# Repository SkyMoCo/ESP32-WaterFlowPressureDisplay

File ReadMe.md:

# ESP32 Water Flow & Pressure Display

Firmware for an ESP32 that reads the well's flow meter and pressure sensor,
shows both on two 1.28" round displays, and publishes everything to MQTT.

It builds on [ESP32-Water-Meter-Monitor](../ESP32-Water-Meter-Monitor) and
keeps that project's pulse qualification, pressure math, NVS persistence and
MQTT topics and payloads, so existing dashboards and history carry on
unchanged. The display wiring follows
[The Solar Universe's two-GC9A01 build](https://thesolaruniverse.wordpress.com/2024/01/02/esp32-microcontroller-with-two-circular-240240-pixel-displays-gca901/),
with the pins moved off the ones the meter already uses.

## Hardware

- DOIT ESP32 DevKit V1 (ESP32-WROOM-32)
- EKM 3/4" pulse meter on GPIO 4, 0-100 PSI sensor on GPIO 34, status LED on
  GPIO 2. These are wired exactly as in the meter project, including the
  1k/100nF/100R flow front end and the 10k/10k pressure divider; see its
  ReadMe for why each part is there.
- 2 × 1.28" 240×240 round TFT, GC9A01 controller, 3.3 V, about 50 mA each

Every connection on one page, including the sensor front ends and the harness
notes for a permanent install: [hardware/WIRING.md](hardware/WIRING.md).

For a permanent install there is a carrier PCB that replaces the expansion
board and the harness. It has screw terminals for power, the sensors and the
LED, and headers for the displays. Gerbers, BOM and pick-and-place are ready
to order: [hardware/pcb](hardware/pcb/README.md).

### Display wiring

| ESP32 | Pressure display | Flow display |
|---|---|---|
| 3V3 | VCC | VCC |
| GND | GND | GND |
| GPIO 18 | SCL (SCLK) | SCL (SCLK) |
| GPIO 23 | SDA (MOSI) | SDA (MOSI) |
| GPIO 16 | DC | DC |
| GPIO 17 | RST | — |
| GPIO 27 | — | RST |
| GPIO 21 | CS | — |
| GPIO 22 | — | CS |
| (BL/BLK, if present) | 3V3 or unconnected | 3V3 or unconnected |

The article puts RST on GPIO 4 and DC on GPIO 2, but those pins are the flow
input and the LED here, so both move. GPIO 16/17 are free on a WROOM-32. On a
WROVER module they belong to the PSRAM, and DC/RST would need other pins
(update `platformio.ini`).

Both displays share every line except CS and RST. The firmware resets both,
then brings both CS pins low for `tft.init()` so both controllers get the init
sequence together. After that, each draw selects only one of them.

RST could be shared as well, since the displays are always reset together, but
one pin per display avoids a Y-split jumper. To share it, wire both RST pins to
GPIO 17 and set `DISPLAY_RST_FLOW` to 17 too.

## Displays

- **Left dial, pressure.** 0-100 PSI arc. It is green between
  `GAUGE_PSI_LOW` and `GAUGE_PSI_HIGH` (30 and 70 by default), red below that
  range and orange above it. Set the thresholds just outside your pressure
  switch's cut-in and cut-out. The footer shows `ONLINE`, `NO MQTT` or
  `NO WIFI`. If the sensor voltage leaves its valid range (open or shorted
  wire), the dial shows `--` and `SENSOR FAULT`.
- **Right dial, flow.** 0-20 GPM arc, with the running gallon total in the
  footer. The arc turns red above `MAX_PLAUSIBLE_GPM`.

The gauge reads flow from the time between the last two pulses. The 5 s
interval average moves in 0.9 GPM steps at low flow, which is too coarse and
slow for a needle. When pulses stop, the reading decays toward zero and reaches
zero after `FLOW_TIMEOUT_MS` (60 s).

Arcs are repainted in place and the numbers are drawn to off-screen sprites,
so the displays don't flicker.

## Demo mode

For bench testing with only the ESP32 and the displays wired up:

```
pio run -e demo -t upload
```

In the VS Code PlatformIO sidebar, use **demo → Upload**.

This builds the same firmware with simulated sensors. Every 2-6 s it picks a
new random pressure and flow and moves toward them smoothly. Some picks land
in the low and high pressure zones, above `MAX_PLAUSIBLE_GPM`, or in a sensor
fault, so every display state appears within a minute or two. The gallon total
starts at 12,345 and rises with the simulated flow. The dial titles read
`DEMO PRESSURE` and `DEMO FLOW` in amber.

Demo mode is kept separate from real data:

- **MQTT:** it publishes to `ranch/water-demo/*` as client
  `pumphouse-esp32-demo`. Fake numbers never reach the real topics, and it
  doesn't disconnect the real board.
- **Saved total:** it never reads or writes flash, so the real board's gallon
  total is safe if you reuse this ESP32 later.
- **Flow input:** GPIO 4 is left unused. With no pull-up resistor fitted, the
  pin would float and count noise as pulses.

Flash the default `esp32doit-devkit-v1` env for real use.

## MQTT

Topics and payloads are the same as in the meter project, with two added
fields:

- `ranch/water/flow`: adds `gpm_inst`, the pulse-period rate the gauge shows,
  next to the existing interval-average `gpm`
- `ranch/water/pressure`: adds `sensor_ok`. Its `psi`/`volts` values are now a
  ~0.5 s moving average instead of a single ADC read.
- `ranch/water/diag` and `ranch/water/status` are unchanged. The boot message
  ends with `display=dual_gc9a01`.

WiFi and MQTT run in their own FreeRTOS task on core 0, so reconnect attempts
never stall the displays.

## Setup

1. Copy [include/secrets.h.template](include/secrets.h.template) to
   `include/secrets.h` and fill it in. It is gitignored.
2. **Client ID:** if this board replaces the old one, leave `MQTT_CLIENT_ID`
   as `pumphouse-esp32`. If both will run at once, change it. Two clients with
   the same ID keep disconnecting each other.
3. **Running total:** the total is stored in the board's own flash, so a
   fresh board starts at 0 gallons. Read the old board's `pulse_count` from
   MQTT before swapping if you want to carry it over.
4. Build and upload with PlatformIO (env `esp32doit-devkit-v1`). TFT_eSPI is
   configured entirely through `build_flags` in
   [platformio.ini](platformio.ini), so don't edit the library's
   `User_Setup.h`.

If the image is mirrored or colours are wrong on your particular modules, try
`DISPLAY_ROTATION` in `main.cpp`, or add `-D TFT_RGB_ORDER=TFT_BGR` /
`-D TFT_INVERSION_ON` to `build_flags`.

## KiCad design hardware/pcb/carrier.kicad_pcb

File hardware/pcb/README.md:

# Carrier PCB

A 2-layer board that replaces the stock ESP32 expansion board and the dupont
harness. The DevKit plugs into it, field wiring lands on screw terminals, and
the displays plug into pin headers.

**To order:** upload [fab/carrier_gerbers.zip](fab/carrier_gerbers.zip) to
JLCPCB, PCBWay or similar. The defaults are fine: 2 layers, 1.6 mm, 1 oz,
HASL. Nothing on this board needs tighter than 0.2 mm track/space or a
0.3 mm via drill.

**For SMD assembly at JLCPCB:** tick *PCB Assembly*, top side, and upload
[fab/carrier_bom_jlc.csv](fab/carrier_bom_jlc.csv) and
[fab/carrier_cpl_jlc.csv](fab/carrier_cpl_jlc.csv). In the placement preview,
check that **Q1**, **D1** (cathode band toward Q1) and **F1** sit on their
pads the right way round. JLC's rotation conventions sometimes differ from
KiCad's for SOT-23 and SMA. Everything through-hole you solder yourself.

## Board

67 × 54 mm. The case's bay was sized around the 67 × 51 expansion board, so
set `exp_wid` to 54 in the case `CONFIG`. See [what the case needs](#the-case).

```
  ┌──────────────────────────────────────────────────────────┐
  │ ○  [J5 pressure disp] [J6 flow disp]   [J7 I2C]        ○ │  headers
  │     ════ channel: SPI bus to both headers ════            │
  │     [ DevKit top row: 1.0in ]                    ┌──────┐ │
  │     [ DevKit top row: 0.9in ]                    │ no   │ │
  │ USB    R6 R7 (I2C pull-ups)                      │copper│ │  DevKit sits
  │ <-     C5                                        │ (ant-│ │  over this,
  │        R5 R1 C3 R2         R3 R4 C4              │ enna)│ │  8.5 mm up
  │     [ DevKit bottom row ]                        └──────┘ │
  │       LED  G FLOW G +5V G SIG   G +5V    F1 Q1 R8 C1 C2   │
  │ ○    [J4 ] [J2   ] [J3       ] [J1  ]    D1             ○ │  terminals
  └──────────────────────────────────────────────────────────┘
          wires enter from the bottom edge
```

- **DevKit (U1):** two 1×15 female headers, USB toward the left wall. The
  bottom row is fixed. The top row has two footprints: one for 1.0" (25.4 mm,
  DOIT DevKit V1) and one for 0.9" (22.86 mm) clones. **Solder a socket into
  only one of them.** The silk marks which is which.
- **Antenna:** neither copper layer has anything under the WROOM antenna end,
  so the ground pour doesn't detune it.
- **Parts under the DevKit:** the 0603 resistors and capacitors sit under the
  DevKit. That's fine because the DevKit sits 8.5 mm up on its sockets.

## Connectors

### Screw terminals: 3.5 mm pitch, wires enter from the board edge

| Ref | Pins (left → right) | Goes to |
|---|---|---|
| J4 LED | LED, G | external status LED, anode to LED. **R5 330 Ω is on the board**, so don't add another. |
| J2 FLOW | FLOW, G | EKM reed switch, either way round. Armor/shield to G here only. |
| J3 PRESSURE | +5V, G, SIG | 0-100 PSI transducer: red, black, signal |
| J1 5V IN | G, +5V | regulated 5 V supply, about 250 mA. **Note G is on the left.** |

Footprint is Phoenix PT 1,5/x-3.5-H. The common blue/green "KF350" / "DB128"
3.5 mm terminals fit the same holes. Buy 2-pin and 3-pin, or click 2-pin
blocks together.

### Headers: 2.54 mm, male

| Ref | Pins (left → right) |
|---|---|
| J5 pressure display | GND, VCC, SCL, SDA, RES, DC, CS |
| J6 flow display | GND, VCC, SCL, SDA, RES, DC, CS |
| J7 I2C | GND, 3V3, SCL, SDA |

J5/J6 follow the pin order printed on the common 7-pin GC9A01 modules, so a
7-way dupont ribbon goes straight across. If your module has an 8th BLK pin,
leave it unconnected; the module pulls it up. **Check your module's order
against the silk before plugging in.** Some makers order them differently, and
then you cross the wires in the ribbon.

## Circuit

Every DevKit pin is the same one the firmware already uses
([src/main.cpp](../../src/main.cpp)), so **no firmware change is needed**.

| Net | DevKit pin | Parts |
|---|---|---|
| FLOW_GPIO | GPIO 4 | R1 1k to 3V3, C3 100 nF to GND, R2 100 Ω to J2 FLOW (the WIRING.md front end) |
| PRES_ADC | GPIO 34 | R3 10k from J3 SIG, R4 10k to GND, C4 100 nF to GND |
| LED_GPIO | GPIO 2 | R5 330 Ω to J4 LED |
| SCLK / MOSI / DC | GPIO 18 / 23 / 16 | both display headers |
| RST_P / CS_P | GPIO 17 / 21 | J5 |
| RST_F / CS_F | GPIO 27 / 22 | J6 |
| SDA / SCL | GPIO 25 / 26 | J7, with R6/R7 4k7 pull-ups to 3V3 |
| +5V | VIN | J3 sensor supply, from J1 through F1, Q1 |
| +3V3 | 3V3 | displays, J7, R1, pull-ups. C5 10 µF bulk. |

**C4 is new.** It's a 100 nF filter across the ADC input. With the 5 kΩ
divider it settles in about 0.5 ms, far faster than the firmware's 0.5 s
average, and it gives the ADC's sampling capacitor a low-impedance source.

### Power input

```
 J1 +5V ──F1 500mA PTC──┬── Q1 AO3401A (P-FET) ──┬── +5V → DevKit VIN, J3
                        │   D        S           │
                     D1 SMAJ5.0A           G ─R8 10k─ GND
                        │                        C1 10µ, C2 100n
                       GND
```

- **Reversed supply:** Q1 stays off and nothing downstream sees it.
  D1 conducts and trips F1.
- **Spike or overvoltage:** D1 clamps it. Unlike a series diode, the
  P-FET drops only millivolts, so the pressure sensor still gets the full
  5 V its 0.5-4.5 V output is scaled against.
- **USB and J1 at the same time:** this is normally fine. DOIT-style DevKits
  have a diode between USB 5 V and VIN, so J1 can't back-feed your computer.
  Clones vary, so check yours has one: a diode on the board next to the USB
  socket. Until you've checked, unplug J1 while programming over USB.

## Parts you solder

| Qty | Part |
|---|---|
| 2 | 1×15 female header, 2.54 mm, 8.5 mm tall (one bottom row, one top row) |
| 2 | 1×7 male header, 2.54 mm |
| 1 | 1×4 male header, 2.54 mm |
| 3 | 2-pin 3.5 mm screw terminal |
| 1 | 3-pin 3.5 mm screw terminal |

Fab-assembled SMD parts are in [the BOM](fab/carrier_bom_jlc.csv). All are
JLCPCB Basic parts except F1 (C315893) and D1 (C83329), which are Extended
and add a small loading fee. Any 1206 PTC around 500 mA hold, and any SMA
5.0 V-standoff unidirectional TVS, will do if those are out of stock.

## The case

Things that change in [../case](../case):

- `exp_wid` 51 → 54. The bay grows 3 mm.
- **The barrel-jack and board-USB holes are no longer needed.** The DevKit USB
  hole stays where it is: the DevKit still points its USB at the left wall,
  centred on the board.
- **Add a cable slot in the bottom wall**, under the terminal row. It spans
  x 11-46 mm from the board's left edge. Measure the wire-entry height on
  your terminal blocks; it's typically 3-6 mm above the board surface.

## Rebuilding

The board is generated, not drawn. Both scripts run in KiCad 10's Python:

```
"%LOCALAPPDATA%\Programs\KiCad\10.0\bin\python.exe" build_pcb.py
"%LOCALAPPDATA%\Programs\KiCad\10.0\bin\python.exe" make_outputs.py
```

[build_pcb.py](build_pcb.py) places and routes everything from the constants
at the top: pin map, terminal order, header positions. It also writes the
DevKit socket footprint into `carrier.pretty/`. [make_outputs.py](make_outputs.py)
refills the ground pours, **refuses to continue unless DRC is clean**, then
writes the Gerbers, drill files, zip, BOM, CPL and renders into `fab/`.

You can open `carrier.kicad_pcb` in KiCad and edit it by hand, but the next
`build_pcb.py` run overwrites the board. Either keep changes in the script, or
stop using the script.

There is **no schematic**. The netlist lives in `DEVKIT_NETS` and the
per-part `two_pin(...)` calls in build_pcb.py, and the table above is its
readable form.

The routing works like this:
- **Display bus:** each display net rises from the DevKit's bottom row on
  B.Cu, through a gap in the top row, into the channel under the headers.
- **Channel:** each net has its own F.Cu level there, so they can reorder into
  the modules' pin order. B.Cu stubs then drop into the header pins.
- **+5 V:** runs on B.Cu along the bottom edge and up the left side.

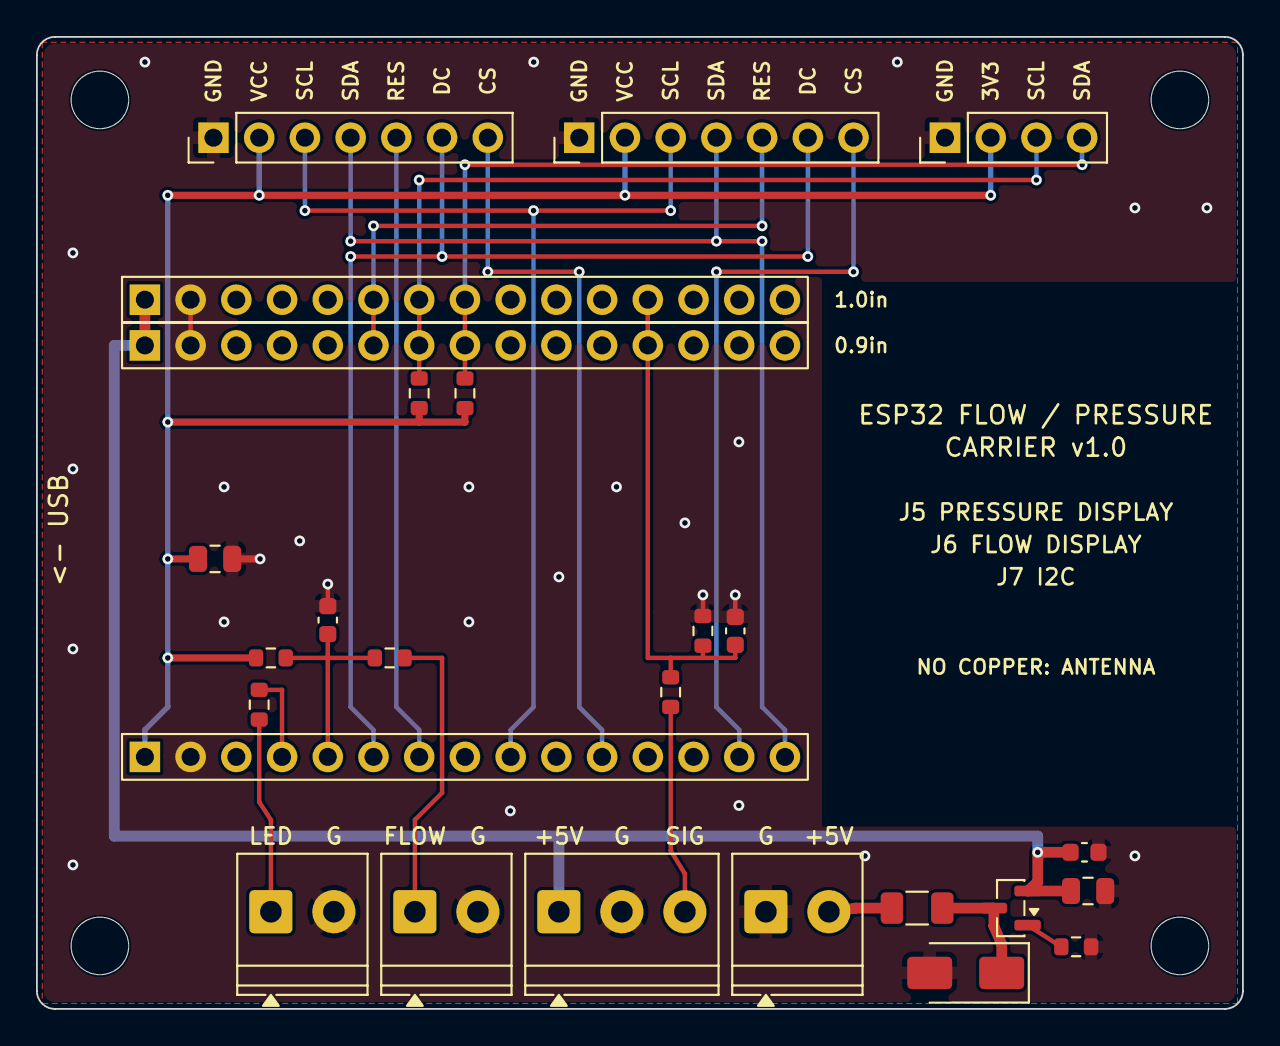
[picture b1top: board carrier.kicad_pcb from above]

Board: 2 copper layers, 67.0 x 54.0 mm, 28 parts (0 on the bottom side), 21 nets.

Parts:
C1, C5: 10uF; C_0805_2012Metric
C2, C3, C4: 100nF; C_0603_1608Metric
D1: SMAJ5.0A; D_SMA
F1: 500mA PTC; Fuse_1206_3216Metric
H1, H2, H3, H4: M3; MountingHole_3.2mm_M3
J1, J2, J4: Screw terminal 2P 3.5mm; TerminalBlock_Phoenix_PT-1,5-2-3.5-H_1x02_P3.50mm_Horizontal
J3: Screw terminal 3P 3.5mm; TerminalBlock_Phoenix_PT-1,5-3-3.5-H_1x03_P3.50mm_Horizontal
J5: Pressure display (GC9A01); PinHeader_1x07_P2.54mm_Vertical
J6: Flow display (GC9A01); PinHeader_1x07_P2.54mm_Vertical
J7: I2C; PinHeader_1x04_P2.54mm_Vertical
Q1: AO3401A; SOT-23
R1: 1k; R_0603_1608Metric
R2: 100R; R_0603_1608Metric
R3, R4, R8: 10k; R_0603_1608Metric
R5: 330R; R_0603_1608Metric
R6, R7: 4k7; R_0603_1608Metric
U1: ESP32 DevKit V1 (30p) on 2x 1x15 female headers; ESP32_DevKit_30P_DualRow

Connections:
+3V3: C5.1, J5.2, J6.2, J7.2, R1.1, R6.1, R7.1, U1.16
+5V: C1.1, C2.1, J3.1, Q1.2, U1.1
+5V_F: D1.1, F1.2, Q1.3
+5V_IN: F1.1, J1.2
CS_F: J6.7, U1.29
CS_P: J5.7, U1.26
DC: J5.6, J6.6, U1.21
FLOW_EXT: J2.1, R2.2
FLOW_GPIO: C3.1, R1.2, R2.1, U1.20
GND: C1.2, C2.2, C3.2, C4.2, C5.2, D1.2, J1.1, J2.2, J3.2, J4.2, J5.1, J6.1, J7.1, R4.2, R8.2, U1.2, U1.17
LED_EXT: J4.1, R5.1
LED_GPIO: R5.2, U1.19
MOSI: J5.4, J6.4, U1.30
PRES_ADC: C4.1, R3.2, R4.1, U1.12
PRES_SIG: J3.3, R3.1
Q1_G: Q1.1, R8.1
RST_F: J6.5, U1.6
RST_P: J5.5, U1.22
SCL: J7.3, R7.2, U1.7
SCLK: J5.3, J6.3, U1.24
SDA: J7.4, R6.2, U1.8

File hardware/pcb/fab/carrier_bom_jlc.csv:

Comment,Designator,Footprint,LCSC Part #
10uF 25V X5R 0805,"C1,C5",C_0805_2012Metric,C15850
100nF,"C2,C3,C4",C_0603_1608Metric,C14663
SMAJ5.0A TVS,D1,D_SMA,C83329
PTC 500mA hold 1206 (Littelfuse 1206L050/15YR),F1,Fuse_1206_3216Metric,C315893
AO3401A P-MOSFET,Q1,SOT-23,C15127
1k,R1,R_0603_1608Metric,C21190
100R,R2,R_0603_1608Metric,C22775
330R,R5,R_0603_1608Metric,C23138
4k7,"R6,R7",R_0603_1608Metric,C23162
10k,"R3,R4,R8",R_0603_1608Metric,C25804

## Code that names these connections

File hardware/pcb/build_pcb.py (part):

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DEVKIT_NETS = {
    ('T', 'VIN'): '+5V', ('T', 'GND'): 'GND', ('B', 'GND'): 'GND',
    ('B', '3V3'): '+3V3',
    ('B', 'D4'): 'FLOW_GPIO', ('T', 'D34'): 'PRES_ADC', ('B', 'D2'): 'LED_GPIO',
    ('B', 'D18'): 'SCLK', ('B', 'D23'): 'MOSI', ('B', 'D16'): 'DC',
    ('B', 'D17'): 'RST_P', ('T', 'D27'): 'RST_F',
    ('B', 'D21'): 'CS_P', ('B', 'D22'): 'CS_F',
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    B.setnet('Q1', 2, '+5V')
    B.setnet('Q1', 3, '+5V_F')
    qg, qs, qd = B.pp('Q1', 1), B.pp('Q1', 2), B.pp('Q1', 3)
    r8a, r8b = B.two_pin('R8', *R0603, qg[0] + 2.7, qg[1] - 1.2, False, 'Q1_G', 'GND', '10k')
    c1a, c1b = B.two_pin('C1', 'Capacitor_SMD', 'C_0805_2012Metric', 58.4, qs[1],
                         False, '+5V', 'GND', '10uF')
    c2a, c2b = B.two_pin('C2', *C0603, 58.2, 8.7, False, '+5V', 'GND', '100nF')
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                         (X33, LV[5])], 0.3)

    # ---- LED: D2 -> R5 -> J4 ----
    r5a, r5b = B.two_pin('R5', *R0603, gap(2), 16.9, True, 'LED_EXT', 'LED_GPIO', '330R')
    j4 = B.pp('J4', 1)
    B.track('LED_EXT', F, [j4, (j4[0], 10.5), (gap(2), 11.5), r5a])
    d2 = (col(3), Y_BOT)
    B.track('LED_GPIO', F, [r5b, (d2[0], r5b[1]), d2])

    # ---- flow front end: 3V3 -R1 1k- D4 -C3 100n- GND, D4 -R2 100R- J2 ----
    YF = 19.5
    r1a, r1b = B.two_pin('R1', *R0603, 13.0, YF, False, '+3V3', 'FLOW_GPIO', '1k')
    B.via('+3V3', X33, YF)
    B.track('+3V3', F, [(X33, YF), r1a], W_3V3)
    d4 = (col(4), Y_BOT)
    B.track('FLOW_GPIO', F, [d4, (d4[0], YF), r1b])
    c3a, c3b = B.two_pin('C3', *C0603, d4[0], 21.6, True, 'FLOW_GPIO', 'GND', '100nF')
    B.track('FLOW_GPIO', F, [(d4[0], YF), c3a])
    B.via('GND', d4[0], 23.6)
    B.track('GND', F, [c3b, (d4[0], 23.6)], W_SIG)
    r2a, r2b = B.two_pin('R2', *R0603, 19.6, YF, False, 'FLOW_GPIO', 'FLOW_EXT', '100R')
    B.track('FLOW_GPIO', F, [(d4[0], YF), r2a])
    j2 = B.pp('J2', 1)
    B.track('FLOW_EXT', F, [r2b, (gap(6), YF), (gap(6), 12.0), (j2[0], 10.5), j2])

    # ---- pressure: J3 SIG -R3 10k- ADC -R4 10k- GND, C4 100n ----
    xs = gap(11)
    r3a, r3b = B.two_pin('R3', *R0603, xs, 17.6, True, 'PRES_SIG', 'PRES_ADC', '10k')
    j3s = B.pp('J3', 3)
    B.track('PRES_SIG', F, [j3s, (j3s[0], 7.5), (xs, 8.8), r3a])
    YA = 19.5
    adc_top = (col(11), Y_TOP_N)
    B.track('PRES_ADC', F, [r3b, (xs, YA), (col(11), YA), adc_top])
    r4a, r4b = B.two_pin('R4', *R0603, 37.0, 21.0, True, 'PRES_ADC', 'GND', '10k')
    c4a, c4b = B.two_pin('C4', *C0603, 38.8, 21.0, True, 'PRES_ADC', 'GND', '100nF')
    B.track('PRES_ADC', F, [(xs, YA), (38.8, YA), c4a])
    B.track('PRES_ADC', F, [(37.0, YA), r4a])
    for gx, (gp) in ((37.0, r4b), (38.8, c4b)):
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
